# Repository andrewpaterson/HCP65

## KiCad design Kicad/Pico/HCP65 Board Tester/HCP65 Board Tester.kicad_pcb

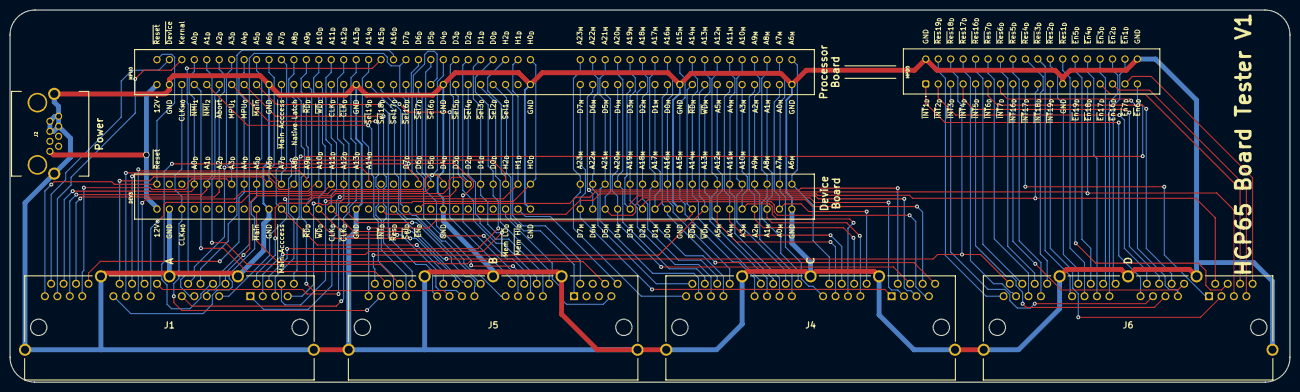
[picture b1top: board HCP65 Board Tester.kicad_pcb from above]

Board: 2 copper layers, 261.1 x 75.9 mm, 8 parts (0 on the bottom side), 127 nets.

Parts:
DEV3: 395-098-520-350; 395098520350
J1, J4, J5, J6: 6339167-2; 63391672
J2: 1-406541-1; 1-406541-1_1
MPD0: 2-5530843-7; 255308437
MPU0: 395-098-520-350; 395098520350

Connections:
/12V: DEV3.B1, J2.1, MPU0.B1
/A0_{D}: DEV3.A4, J1.D4, MPU0.A4
/A0_{M}: DEV3.D17, J4.B8, MPU0.D17
/A1_{D}: DEV3.A5, J1.D5, MPU0.A5
/A1_{M}: DEV3.D16, J4.B7, MPU0.D16
/A2_{D}: DEV3.A6, J1.D6, MPU0.A6
/A2_{M}: DEV3.D15, J4.B6, MPU0.D15
/A3_{D}: DEV3.A7, J1.D7, MPU0.A7
/A3_{M}: DEV3.D14, J4.B5, MPU0.D14
/A4_{D}: DEV3.A8, J1.D8, MPU0.A8
/A4_{M}: DEV3.D13, J4.B4, MPU0.D13
/A5_{D}: DEV3.A9, J1.C1, MPU0.A9
/A5_{M}: DEV3.D12, J4.B3, MPU0.D12
/A6_{D}: DEV3.A10, J1.C2, MPU0.A10
/A6_{M}: DEV3.C18, J4.B2, MPU0.C18
/A7_{D}: DEV3.A11, J1.C3, MPU0.A11
/A7_{M}: DEV3.C17, J4.B1, MPU0.C17
/A8_{D}: DEV3.A12, J1.C4, MPU0.A12
/A8_{M}: DEV3.C16, J4.C8, MPU0.C16
/A9_{D}: DEV3.A13, J1.C5, MPU0.A13
/A9_{M}: DEV3.C15, J4.C7, MPU0.C15
/A10_{D}: DEV3.A14, J1.C6, MPU0.A14
/A10_{M}: DEV3.C14, J4.C6, MPU0.C14
/A11_{D}: DEV3.A15, J1.C7, MPU0.A15
/A11_{M}: DEV3.C13, J4.C5, MPU0.C13
/A12_{D}: DEV3.A16, J1.C8, MPU0.A16
/A12_{M}: DEV3.C12, J4.C4, MPU0.C12
/A13_{D}: DEV3.A17, J1.B1, MPU0.A17
/A13_{M}: DEV3.C11, J4.C3, MPU0.C11
/A14_{D}: DEV3.A18, J1.B2, MPU0.A18
/A14_{M}: DEV3.C10, J4.C2, MPU0.C10
/A15_{D}: J1.B3, MPU0.A19
/A15_{M}: DEV3.C9, J4.C1, MPU0.C9
/A16_{D}: J1.B4, MPU0.A20
/A16_{M}: DEV3.C8, J4.D8, MPU0.C8
/A17_{M}: DEV3.C7, J4.D7, MPU0.C7
/A18_{M}: DEV3.C6, J4.D6, MPU0.C6
/A19_{M}: DEV3.C5, J4.D5, MPU0.C5
/A20_{M}: DEV3.C4, J4.D4, MPU0.C4
/A21_{M}: DEV3.C3, J4.D3, MPU0.C3
/A22_{M}: DEV3.C2, J4.D2, MPU0.C2
/A23_{M}: DEV3.C1, J4.D1, MPU0.C1
/CLK_{D}: DEV3.B15, J5.C6, MPU0.B15
/CLK_{M0}: DEV3.B3, J5.D3, MPU0.B3
/D0_{D}: DEV3.A28, J1.A4, MPU0.A28
/D0_{M}: DEV3.D8, J4.A8, MPU0.D8
/D1_{D}: DEV3.A27, J1.A3, MPU0.A27
/D1_{M}: DEV3.D7, J4.A7, MPU0.D7
/D2_{D}: DEV3.A26, J1.A2, MPU0.A26
/D2_{M}: DEV3.D6, J4.A6, MPU0.D6
/D3_{D}: DEV3.A25, J1.A1, MPU0.A25
/D3_{M}: DEV3.D5, J4.A5, MPU0.D5
/D4_{D}: DEV3.A24, J1.B8, MPU0.A24
/D4_{M}: DEV3.D4, J4.A4, MPU0.D4
/D5_{D}: DEV3.A23, J1.B7, MPU0.A23
/D5_{M}: DEV3.D3, J4.A3, MPU0.D3
/D6_{D}: DEV3.A22, J1.B6, MPU0.A22
/D6_{M}: DEV3.D2, J4.A2, MPU0.D2
/D7_{D}: DEV3.A21, J1.B5, MPU0.A21
/D7_{M}: DEV3.D1, J4.A1, MPU0.D1
/GND: DEV3.B2, DEV3.B10, DEV3.B17, DEV3.B24, DEV3.B31, DEV3.D9, DEV3.D18, J1.MH1, J1.MH2, J1.MH3, J1.MH4, J1.MH5, J2.5, J2.6, J2.7, J2.8, J2.MH1, J2.MH2, J4.MH1, J4.MH2, J4.MH3, J4.MH4, J4.MH5, J5.MH1, J5.MH2, J5.MH3, J5.MH4, J5.MH5, J6.MH1, J6.MH2, J6.MH3, J6.MH4, J6.MH5, MPD0.2, MPD0.23, MPD0.36, MPU0.B2, MPU0.B10, MPU0.B17, MPU0.B24, MPU0.B31, MPU0.D9, MPU0.D18
/H0_{D}: DEV3.A31, J1.A7, MPU0.A31
/H1_{D}: DEV3.A30, J1.A6, MPU0.A30
/H2_{D}: DEV3.A29, J1.A5, MPU0.A29
/Kernal: J1.D3, MPU0.A3
/MPU0_{M}: J5.D8, MPU0.B8
/MPU1_{M}: J5.D7, MPU0.B7
/Native Latch: J5.C3, MPU0.B12
/~ABORT: J5.D6, MPU0.B6
/~CLK_{D}: DEV3.B16, J5.C7, MPU0.B16
/~Device: J1.D2, MPU0.A2
/~Enable_{Device}1: J6.C8, MPD0.34
/~Enable_{Device}2: J6.C7, MPD0.32
/~Enable_{Device}3: J6.C6, MPD0.30
/~Enable_{Device}4: J6.C5, MPD0.28
/~Enable_{Device}5: J6.C4, MPD0.26
/~Enable_{Device}6: J1.A8, MPD0.35
/~Enable_{Device}7: J6.A8, MPD0.33
/~Enable_{Device}16: J6.A7, MPD0.31
/~Enable_{Device}17: J6.A6, MPD0.29
/~Enable_{Device}18: DEV3.B22, J6.A5, MPD0.27
/~Enable_{Device}19: J6.A4, MPD0.25
/~Interrupt_{Device}1: J6.B1, MPD0.1
/~Interrupt_{Device}2: J6.B2, MPD0.3
/~Interrupt_{Device}3: J6.B3, MPD0.5
/~Interrupt_{Device}4: J6.B4, MPD0.7
/~Interrupt_{Device}5: J6.B5, MPD0.9
/~Interrupt_{Device}6: J6.B6, MPD0.11
/~Interrupt_{Device}7: J6.B7, MPD0.13
/~Interrupt_{Device}16: J6.B8, MPD0.15
/~Interrupt_{Device}17: J6.A1, MPD0.17
/~Interrupt_{Device}18: DEV3.B19, J6.A2, MPD0.19
/~Interrupt_{Device}19: J6.A3, MPD0.21
/~Main Access_{M0}: DEV3.B11, J5.C2, MPU0.B11
/~Main3: DEV3.B9, J5.A6
/~Main MPU: J5.C1, MPU0.B9
/~Memory Hi_{ Device}: DEV3.B30, J5.A8
/~Memory Lo_{ Device}: DEV3.B29, J5.A7
/~NMI_{1}: J5.D4, MPU0.B4
/~NMI_{2}: J5.D5, MPU0.B5
/~RD_{D}: DEV3.B13, J5.C4, MPU0.B13
/~RD_{M}: DEV3.D10, J5.D1, MPU0.D10
/~Reset: DEV3.A1, J1.D1, MPU0.A1
/~Reset_{Device}1: J6.C3, MPD0.24
/~Reset_{Device}2: J6.C2, MPD0.22
/~Reset_{Device}3: J6.C1, MPD0.20
/~Reset_{Device}4: J6.D8, MPD0.18
/~Reset_{Device}5: J6.D7, MPD0.16
/~Reset_{Device}6: J6.D6, MPD0.14
/~Reset_{Device}7: J6.D5, MPD0.12
/~Reset_{Device}16: J6.D4, MPD0.10
/~Reset_{Device}17: J6.D3, MPD0.8
/~Reset_{Device}18: DEV3.B20, J6.D2, MPD0.6
/~Reset_{Device}19: J6.D1, MPD0.4
/~Select_{Device}1: J5.A2, MPU0.B29
/~Select_{Device}2: J5.A1, MPU0.B28
/~Select_{Device}3: J5.B8, MPU0.B27
/~Select_{Device}4: J5.B7, MPU0.B26
/~Select_{Device}5: J5.B6, MPU0.B25
/~Select_{Device}6: J5.B5, MPU0.B23
/~Select_{Device}7: J5.B4, MPU0.B22
/~Select_{Device}16: J5.B3, MPU0.B21
/~Select_{Device}17: J5.B2, MPU0.B20
/~Select_{Device}18: DEV3.B21, J5.B1, MPU0.B19
/~Select_{Device}19: J5.C8, MPU0.B18
/~WD_{D}: DEV3.B14, J5.C5, MPU0.B14
/~WD_{M}: DEV3.D11, J5.D2, MPU0.D11

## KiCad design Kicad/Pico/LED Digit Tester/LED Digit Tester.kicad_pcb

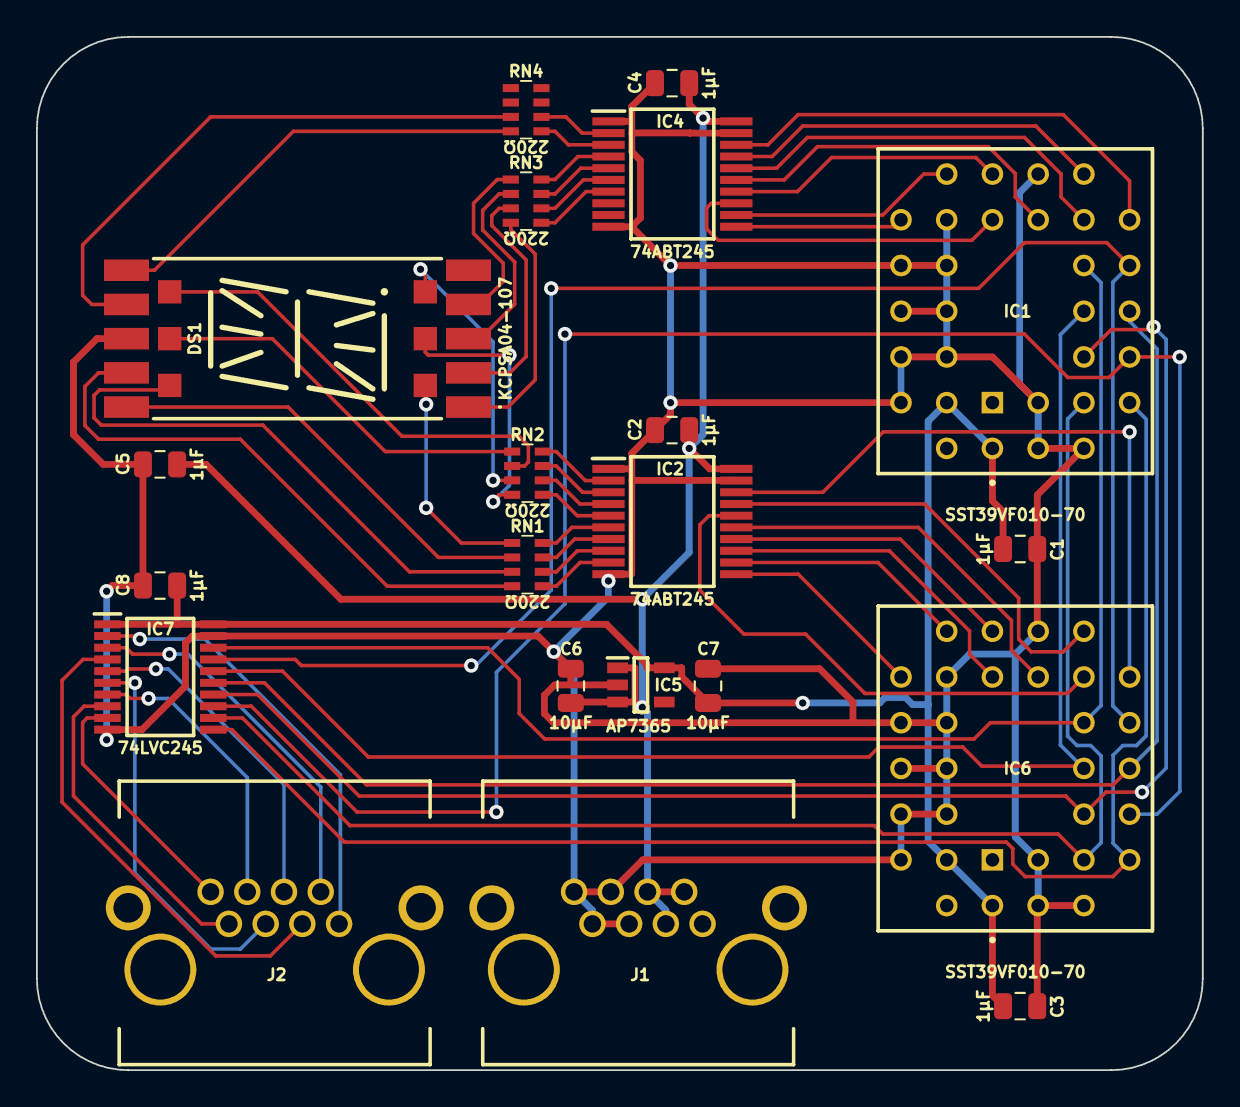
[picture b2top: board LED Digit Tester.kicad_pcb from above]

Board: 2 copper layers, 64.8 x 57.4 mm, 21 parts (0 on the bottom side), 63 nets.

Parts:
C1, C2, C3, C4, C5, C8: 1μF; C_0805
C6, C7: 10µF; C_0805
DS1: KCPSA04-107; KCPSA04107
IC1, IC6: SST39VF010-70-4I-NHE; 5408803224008
IC2, IC4: SN74ABT245BDBR; SOP65P780X200-20N
IC5: AP7365-33WG-7; SOT95P285X130-5N
IC7: 74LVC245AT20; SOP65P640X120-20N
J1, J2: 1-406541-1; 1-406541-1_1
RN1, RN2, RN3, RN4: CAY16-221J4LF; CAY16-F4

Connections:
/3.3V: C1.1, C3.1, C7.1, C8.1, IC1.31 (~WE), IC1.32 (3V), IC5.5 (3.3VOut), IC6.31 (~WE), IC6.32 (3V), IC7.1 (DIR), IC7.20 (3V)
/5V: C2.1, C4.1, C5.1, C6.1, IC2.20 (5V), IC4.20 (5V), IC5.1 (6VIn), IC5.3 (EN), J1.2, J1.3, J1.4
/A0: IC1.12 (A0), IC6.12 (A0), IC7.18 (B0)
/A1: IC1.11 (A1), IC6.11 (A1), IC7.17 (B1)
/A2: IC1.10 (A2), IC6.10 (A2), IC7.16 (B2)
/A3: IC1.9 (A3), IC6.9 (A3), IC7.15 (B3)
/A4: IC1.8 (A4), IC6.8 (A4), IC7.14 (B4)
/A5: IC1.7 (A5), IC6.7 (A5), IC7.13 (B5)
/A6: IC1.6 (A6), IC6.6 (A6), IC7.12 (B6)
/A7: IC1.5 (A7), IC6.5 (A7), IC7.11 (B7)
/GND: C1.2, C2.2, C3.2, C4.2, C5.2, C6.2, C7.2, C8.2, DS1.14 (Cathode), IC1.2 (A16), IC1.3 (A15), IC1.4 (A12), IC1.16 (GND), IC1.22 (~CE), IC1.23 (A10), IC1.24 (~OE), IC1.25 (A11), IC1.26 (A9), IC1.27 (A8), IC1.28 (A13), IC1.29 (A14), IC2.1 (DIR), IC2.10 (GND), IC2.19 (~OE), IC4.1 (DIR), IC4.10 (GND), IC4.19 (~OE), IC5.2 (GND), IC6.2 (A16), IC6.3 (A15), IC6.4 (A12), IC6.16 (GND), IC6.22 (~CE), IC6.23 (A10), IC6.24 (~OE), IC6.25 (A11), IC6.26 (A9), IC6.27 (A8), IC6.28 (A13), IC6.29 (A14), IC7.10 (GND), IC7.19 (~OE), J1.5, J1.6, J1.7, J1.8
/LED A-Seg: IC2.2 (A0), RN2.8 (R1)
/LED B-Seg: IC2.3 (A1), RN2.7 (R2)
/LED C-Seg: IC2.4 (A2), RN2.6 (R3)
/LED D-Seg: IC2.5 (A3), RN2.5 (R4)
/LED E-Seg: IC2.6 (A4), RN1.8 (R1)
/LED F-Seg: IC2.7 (A5), RN1.7 (R2)
/LED G-Seg: IC2.8 (A6), RN1.6 (R3)
/LED H-Seg: IC2.9 (A7), RN1.5 (R4)
/LED J-Seg: IC4.2 (A0), RN4.6 (R3)
/LED K-Seg: IC4.3 (A1), RN4.5 (R4)
/LED L-Seg: IC4.4 (A2), RN3.8 (R1)
/LED M-Seg: IC4.5 (A3), RN3.7 (R2)
/LED N-Seg: IC4.6 (A4), RN3.6 (R3)
/LED P-Seg: IC4.7 (A5), RN3.5 (R4)
/LED Ω A-Seg: DS1.10 (A-Seg), RN2.1 (R1)
/LED Ω B-Seg: DS1.11 (B-Seg), RN2.2 (R2)
/LED Ω C-Seg: DS1.6 (C-Seg), RN2.3 (R3)
/LED Ω D-Seg: DS1.7 (D-Seg), RN2.4 (R4)
/LED Ω E-Seg: DS1.8 (E-Seg), RN1.1 (R1)
/LED Ω F-Seg: DS1.16 (F-Seg), RN1.2 (R2)
/LED Ω G-Seg: DS1.9 (G-Seg), RN1.3 (R3)
/LED Ω H-Seg: DS1.15 (H-Seg), RN1.4 (R4)
/LED Ω J-Seg: DS1.13 (J-Seg), RN4.3 (R3)
/LED Ω K-Seg: DS1.12 (K-Seg), RN4.4 (R4)
/LED Ω L-Seg: DS1.4 (L-Seg), RN3.1 (R1)
/LED Ω M-Seg: DS1.3 (M-Seg), RN3.2 (R2)
/LED Ω N-Seg: DS1.2 (N-Seg), RN3.3 (R3)
/LED Ω P-Seg: DS1.1 (P-Seg), RN3.4 (R4)
/OP0: IC7.2 (A0), J2.1
/OP1: IC7.3 (A1), J2.2
/OP2: IC7.4 (A2), J2.3
/OP3: IC7.5 (A3), J2.4
/OP4: IC7.6 (A4), J2.5
/OP5: IC7.7 (A5), J2.6
/OP6: IC7.8 (A6), J2.7
/OP7: IC7.9 (A7), J2.8
unnamed: IC1.13 (DQ0), IC4.18 (B0)
unnamed: IC1.14 (DQ1), IC4.17 (B1)
unnamed: IC1.15 (DQ2), IC4.16 (B2)
unnamed: IC1.17 (DQ3), IC4.15 (B3)
unnamed: IC1.18 (DQ4), IC4.14 (B4)
unnamed: IC1.19 (DQ5), IC4.13 (B5)
unnamed: IC1.20 (DQ6), IC4.12 (B6)
unnamed: IC1.21 (DQ7), IC4.11 (B7)
unnamed: IC2.18 (B0), IC6.13 (DQ0)
unnamed: IC2.17 (B1), IC6.14 (DQ1)
unnamed: IC2.16 (B2), IC6.15 (DQ2)
unnamed: IC2.15 (B3), IC6.17 (DQ3)
unnamed: IC2.14 (B4), IC6.18 (DQ4)
unnamed: IC2.13 (B5), IC6.19 (DQ5)
unnamed: IC2.12 (B6), IC6.20 (DQ6)
unnamed: IC2.11 (B7), IC6.21 (DQ7)

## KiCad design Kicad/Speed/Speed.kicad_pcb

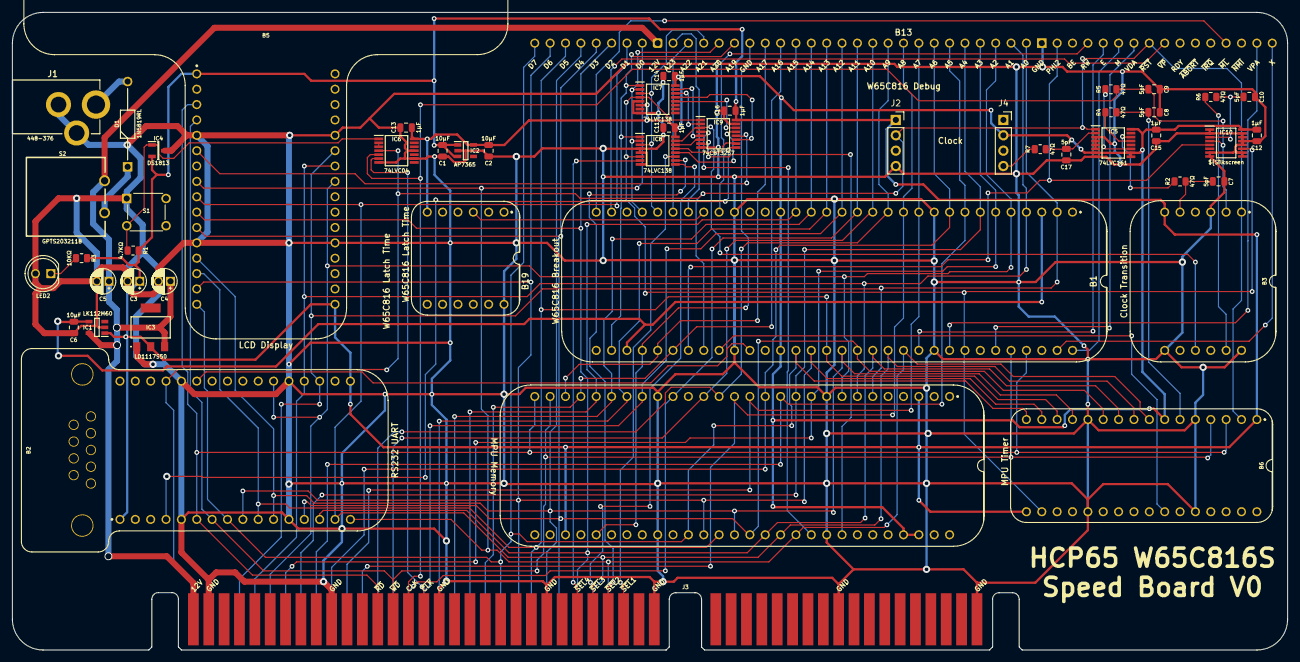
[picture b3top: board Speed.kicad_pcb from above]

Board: 2 copper layers, 210.8 x 105.4 mm, 50 parts (0 on the bottom side), 89 nets.

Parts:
B1: W65C816 Breakout; HCP65_W65C816_Breakout
B2: UART RS232; HCP65_RS232_UART
B3: Clock Transition; HCP65_Clock_Transition
B4: MPU Memory; HCP65_MPU_Memory
B5: LCD Display; HCP65_LCD_Display
B6: MPU Timer; HCP65_MPU_Timer
B13: W65C816 Debug; HCP65_W65C816_Debug_Display
B19: W65C816_Latch_Time; HCP65_W65C816_Latch_Time
C1, C2, C6: 10µF; C_0805
C3: 100μF; CP_Radial_D4.0mm_P2.00mm
C4, C5: 10μF; CP_Radial_D4.0mm_P2.00mm
C7, C8, C9, C10, C17: 5pF; C_0805
C11, C12, C13, C14, C15, C16: 1µF; C_0805
D1: 1N5819RL; DIOAD1414W86L464D238
IC1: LK112M60TR; SOT95P285X130-5N
IC2: AP7365-33WG-7; SOT95P285X130-5N
IC3: LD1117S50C; LD1117S33C
IC4: DS1813R-10+T&R; SOT95P237X112-3N
IC5: 74LVC161PW,112; SOP65P640X110-16N
IC6: 74LVC04APW,118; SOP65P640X110-14N
IC7, IC8: 74LVC138APW-Q100J; SOP65P640X110-16N
IC9: SN74CBT3257CPWR; SOP65P640X120-16N
IC10: PI3B3251QE; SOP64P599X175-16N
J1: 448-376; 448376
J2, J4: Conn_01x04_Socket; PinSocket_1x04_P2.54mm_Vertical
J3: 395-098-520-350; 98pin Edge Connector
LED2: Red; LED_D5.0mm
R1: 4.7KΩ; R_0805
R2, R4, R5, R6, R7: 47Ω; R_0805
R3: 10KΩ; R_0805
S1: DTS-62N-V; DTS62NV
S2: GPTS203211B

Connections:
6.25MHZ: B3.2 (Slow_Clock), C9.1, IC6.5 (3A), IC10.4 (I0), J3.B15, R5.1
12V: B13.9 (12V), C4.1, C5.1, IC1.5 (14VIn), IC3.3 (15VIn), J3.B1, S2.2
/3.3V: B1.20 (BE), B1.45 (DE), B4.53 (~Special), B4.54 (~Main), B6.7 (~NMI_Rate_Select), B19.6 (3.3V), C2.1, C11.1, C12.1, C13.1, C14.1, C15.1, IC2.5 (3.3VOut), IC5.7 (CEP), IC5.9 (~PE), IC5.10 (CET), IC5.16 (3V), IC6.14 (3V), IC7.6 (E3), IC7.16 (3V), IC8.16 (3V), IC10.16 (3V), J4.2
/5V: B2.1 (5V), B2.17 (5V), B3.6 (5V), B4.3 (5V), B4.31 (5V), B5.1 (5V), B5.17 (5V), B6.1 (5V), B6.17 (5V), C1.1, C3.1, C16.1, IC1.1 (~SHDN), IC2.1 (6VIn), IC2.3 (EN), IC3.2 (5.0VOut), IC3.4 (5.0VOut), IC4.2 (5V), IC9.16 (5V), J2.1, R1.2, R3.2
/12V Forward: D1.1, S2.1
/12V Socket: D1.2, J1.INNER (VCC)
/25MHZ: B6.6 (CLK), C8.1, R4.1
/50MHZ: B3.5 (Fast_Clock), C7.1, R2.1
/A17: B1.37 (BA1), B4.26 (A17), B13.16 (A17)
/A18: B1.36 (BA2), B4.33 (A18), B13.15 (A18)
/A19: B1.34 (BA3), B13.14 (A19), IC7.1 (A0), IC8.1 (A0)
/A20: B1.29 (BA4), B13.13 (A20), IC7.2 (A1), IC8.2 (A1)
/A21: B1.28 (BA5), B13.12 (A21), IC7.3 (A2), IC8.3 (A2)
/A22: B1.27 (BA6), B13.11 (A22)
/A23: B1.26 (BA7), B13.10 (A23)
/Address Valid: B1.22 (Address_Valid), IC6.13 (6A)
/Bank Latch: B1.30 (Bank_Latch), B19.9 (~Data_Output)
/CLK: J4.4, R7.2
/Clock: C10.1, IC10.3 (I1), R6.1
/E: B1.54 (E), B13.38 (E)
/M: B1.64 (M), B13.39 (M)
/Native Latch: B1.57 (Native_Latch), B6.18 (~Hold), IC7.4 (~E1), IC8.6 (E3), IC9.1 (S), IC10.11 (S0)
/PHI2: B1.39 (PHI2), B13.35 (PHI2), IC10.5 (Y)
/Reset: IC6.2 (1Y), IC6.3 (2A)
/R~W: B1.24 (R~W), B13.37 (R~W)
/VDA: B1.59 (VDA), B13.40 (VDA)
/VPA: B1.56 (VPA), B13.48 (VPA)
/W65C816V: B1.3 (5V), B1.35 (5V), C6.1, IC1.4 (5.0VOut)
/X: B1.63 (X), B13.49 (X)
/~Address Valid: B4.1 (~Address_Valid), IC6.12 (6Y)
/~INT: B1.43 (~IRQ), B2.27 (~INT)
/~LCD: B5.6 (~CS), IC9.12 (4A)
/~LCD_{E}: IC7.12 (~Y3), IC9.14 (4B1)
/~LCD_{N}: IC8.12 (~Y3), IC9.13 (4B2)
/~ML: B1.32 (~ML), B13.46 (~ML)
/~NMI: B1.41 (~NMI), B6.26 (~Set_Timer)
/~PHI2: B1.25 (~PHI2_{OUT}), B19.3 (~PHI2)
/~RAM: B4.47 (~RAM), IC9.4 (1A)
/~RAM_{E}: IC7.14 (~Y1), IC9.2 (1B1)
/~RAM_{N}: B3.9 (~Select_Fast), IC8.15 (~Y0), IC9.3 (1B2)
/~ROM: B4.49 (~ROM), IC9.7 (2A)
/~ROM_{E}: IC7.15 (~Y0), IC9.5 (2B1)
/~ROM_{N}: IC8.14 (~Y1), IC9.6 (2B2)
/~Reset Switch: IC4.1 (~RST), IC6.1 (1A), R1.1, S1.3 (N1)
/~Trans Out: B1.58 (~Data_Output), B19.10 (Bank_Latch)
/~UART: B2.4 (~CS), IC9.9 (3A)
/~UART_{E}: IC7.13 (~Y2), IC9.11 (3B1)
/~UART_{N}: IC8.13 (~Y2), IC9.10 (3B2)
/~VP: B1.31 (~VP), B13.42 (~VP)
A0: B1.2 (A0), B2.19 (A0), B4.6 (A0), B5.27 (A0), B13.33 (A0), J3.A4
A1: B1.4 (A1), B2.20 (A1), B4.7 (A1), B5.26 (A1), B13.32 (A1), J3.A5
A2: B1.5 (A2), B2.22 (A2), B4.8 (A2), B5.25 (A2), B13.31 (A2), J3.A6
A3: B1.6 (A3), B4.10 (A3), B13.30 (A3), J3.A7
A4: B1.7 (A4), B4.11 (A4), B13.29 (A4), J3.A8
A5: B1.8 (A5), B4.12 (A5), B13.28 (A5), J3.A9
A6: B1.9 (A6), B4.13 (A6), B13.27 (A6), J3.A10
A7: B1.11 (A7), B4.14 (A7), B13.26 (A7), J3.A11
A8: B1.12 (A8), B4.15 (A8), B13.25 (A8), J3.A12
A9: B1.13 (A9), B4.16 (A9), B13.24 (A9), J3.A13
A10: B1.14 (A10), B4.17 (A10), B13.23 (A10), J3.A14
A11: B1.15 (A11), B4.19 (A11), B13.22 (A11), J3.A15
A12: B1.16 (A12), B4.21 (A12), B13.21 (A12), J3.A16
A13: B1.17 (A13), B4.22 (A13), B13.20 (A13), J3.A17
A14: B1.18 (A14), B4.23 (A14), B13.19 (A14), J3.A18
A15: B1.19 (A15), B4.24 (A15), B13.18 (A15), J3.A19
A16: B1.38 (BA0), B4.25 (A16), B13.17 (A16), J3.A20
D0: B1.53 (D0), B2.16 (D0), B4.46 (D0), B5.8 (D0), B6.8 (D0), B13.8 (D0), J3.A28
D1: B1.52 (D1), B2.15 (D1), B4.45 (D1), B5.9 (D1), B6.9 (D1), B13.7 (D1), J3.A27
D2: B1.51 (D2), B2.14 (D2), B4.44 (D2), B5.10 (D2), B6.10 (D2), B13.6 (D2), J3.A26
D3: B1.50 (D3), B2.13 (D3), B4.43 (D3), B5.11 (D3), B6.11 (D3), B13.5 (D3), J3.A25
D4: B1.49 (D4), B2.11 (D4), B4.42 (D4), B5.13 (D4), B6.13 (D4), B13.4 (D4), J3.A24
D5: B1.48 (D5), B2.10 (D5), B4.41 (D5), B5.14 (D5), B6.14 (D5), B13.3 (D5), J3.A23
D6: B1.47 (D6), B2.9 (D6), B4.40 (D6), B5.15 (D6), B6.15 (D6), B13.2 (D6), J3.A22
D7: B1.46 (D7), B2.8 (D7), B4.39 (D7), B5.16 (D7), B6.16 (D7), B13.1 (D7), J3.A21
GND: B1.10 (GND), B1.23 (GND), B1.42 (GND), B1.55 (GND), B2.5 (GND), B2.12 (GND), B2.21 (GND), B2.28 (GND), B3.3 (GND), B3.7 (GND), B3.12 (GND), B4.9 (GND), B4.20 (GND), B4.37 (GND), B4.48 (GND), B5.5 (GND), B5.12 (GND), B5.21 (GND), B5.28 (GND), B6.5 (GND), B6.12 (GND), B6.21 (GND), B6.28 (GND), B13.34 (GND), B19.12 (GND), C1.2, C2.2, C3.2, C4.2, C5.2, C6.2, C7.2, C8.2, C9.2, C10.2, C11.2, C12.2, C13.2, C14.2, C15.2, C16.2, C17.2, IC1.2 (GND), IC2.2 (GND), IC3.1 (GND), IC4.3 (GND), IC5.3 (D0), IC5.4 (D1), IC5.5 (D2), IC5.6 (D3), IC5.8 (GND), IC6.7 (GND), IC6.9 (4A), IC6.11 (5A), IC7.5 (~E2), IC7.8 (GND), IC8.4 (~E1), IC8.5 (~E2), IC8.8 (GND), IC9.8 (GND), IC9.15 (~OE), IC10.1 (I3), IC10.2 (I2), IC10.7 (~OE), IC10.8 (GND), IC10.9 (S2), IC10.10 (S1), IC10.12 (I7), IC10.13 (I6), IC10.14 (I5), IC10.15 (I4), J1.SHL1 (GND), J1.SHL2 (GND), J2.4, J3.B2, J3.B10, J3.B17, J3.B24, J3.B31, J3.D9, J3.D18, LED2.2 (A), S1.1 (C1)
unnamed: B3.11 (Clock), R6.2
unnamed: C17.1, IC5.2 (CP), R7.1
unnamed: IC5.14 (Q0), R2.2
unnamed: IC5.13 (Q1), R4.2
unnamed: IC5.11 (Q3), R5.2
unnamed: LED2.1 (K), R3.1
~6.25MHZ: IC6.6 (3Y), J3.B16
~RD: B1.61 (~RD), B2.6 (~RD), B4.28 (~RD), B5.3 (~RD), B6.3 (~RD), J3.B13
~Reset: B1.40 (~Reset), B2.29 (~Reset), B3.1 (~Reset), B6.2 (~Reset), B13.41 (~RES), IC5.1 (~MR), IC6.4 (2Y), J2.2, J3.A1
~Select_{Device}1: IC8.11 (~Y4), J3.B29
~Select_{Device}2: IC8.10 (~Y5), J3.B28
~Select_{Device}3: IC8.9 (~Y6), J3.B27
~Select_{Device}4: IC8.7 (~Y7), J3.B26
~WD: B1.60 (~WD), B2.7 (~WD), B4.27 (~WD), B5.4 (~WD), B6.4 (~WD), J3.B14

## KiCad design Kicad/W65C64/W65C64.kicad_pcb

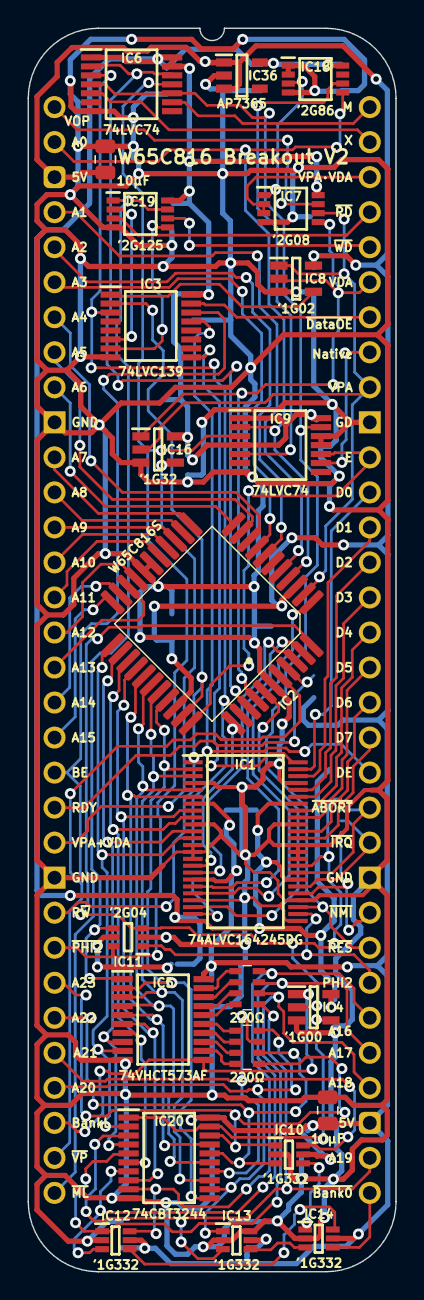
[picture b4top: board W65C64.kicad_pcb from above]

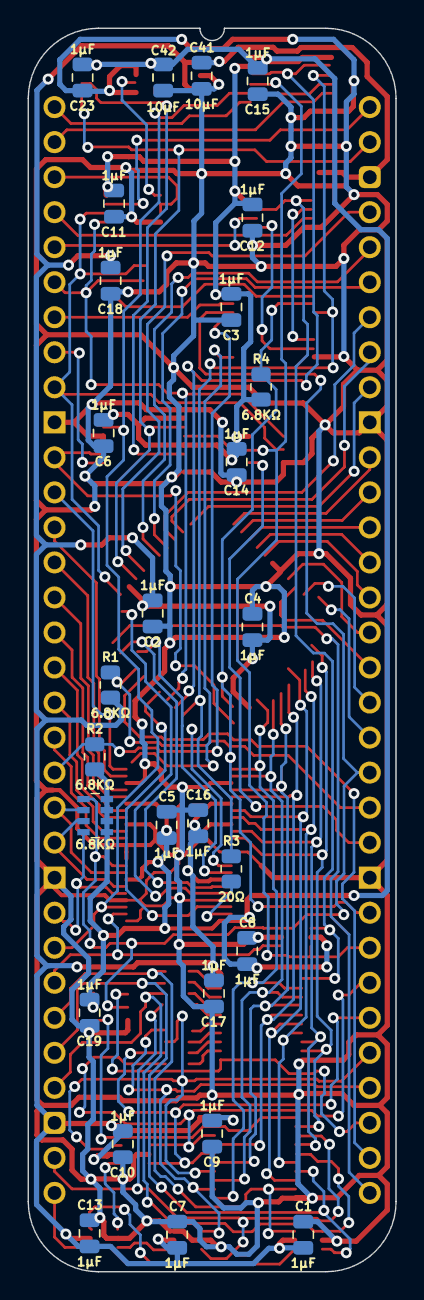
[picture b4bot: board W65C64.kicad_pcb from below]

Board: 2 copper layers, 26.7 x 90.2 mm, 51 parts (27 on the bottom side), 96 nets.

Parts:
C1, C2, C3, C4, C5, C6, C7, C8, C9, C10, C11, C12, C13, C14, C15, C16, C17, C18, C19, C23: 1μF; C_0805
C20, C21, C41, C42: 10μF; C_0805
IC1: 74ALVC164245DGG,11; SOP50P810X120-48N
IC2: W65C816S6TQG-14; W65C816 PLCC 0.8mm 44 Pin
IC3: 74LVC139PW,118; SOP65P640X110-16N
IC4: 74LVC1G00GV,125; SOT95P275X110-5N
IC5: 74VHCT573AFT; SOP65P640X120-20N
IC6, IC9: 74LVC74APW,118; SOP65P640X110-14N
IC7: 74LVC2G08DP-Q100H; SOP65P400X110-8N
IC8: 74LVC1G02GV,125; SOT95P275X110-5N
IC10, IC12, IC13, IC14: SN74LVC1G332DCKRG4; SOT65P210X110-6N
IC11: 74LVC2G04GW-Q100H; SOP65P210X110-6N
IC16: 74LVC1G32GV,125; SOT95P275X110-5N
IC18: 74LVC2G86DP,125; SOP65P400X110-8N
IC19: 74LVC2G125DP,125; SOP65P400X110-8N
IC20: SN74CBT3244CPWR; SOP65P640X120-20N
IC36: AP7365-33WG-7; SOT95P285X130-5N
J7: Board 2x32 W22.86mm; DIP-64_Board_W22.86mm
R1, R2, R4: 6.8KΩ; R_0805
R3: 20Ω; R_0805
RN1, RN2: CAY16-221J4LF; CAY16-F4
RN4: CAY16-472J4LF; CAY16-F4

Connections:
5V: C1.1, C2.1, C4.1, C7.1, C9.1, C10.1, C13.1, C16.1, C17.1, C18.1, C20.1, C21.1, C41.1, IC1.7 (5V), IC1.18 (5V), IC2.9 (VCC), IC2.37 (VCC), IC5.20 (5V), IC8.5 (3V), IC10.5 (3V), IC12.5 (3V), IC13.5 (3V), IC14.5 (3V), IC20.20 (5V), IC36.1 (6VIn), IC36.3 (EN), J7.3, J7.35, R1.1
/3.3V: C3.1, C5.1, C6.1, C8.1, C11.1, C12.1, C14.1, C15.1, C19.1, C23.1, C42.1, IC1.24 (2DIR), IC1.31 (3V), IC1.42 (3V), IC3.16 (3V), IC4.5 (3V), IC6.1 (~1RD), IC6.13 (~2RD), IC6.14 (3V), IC7.8 (3V), IC9.1 (~1RD), IC9.4 (~1SD), IC9.14 (3V), IC11.5 (3V), IC16.5 (3V), IC18.8 (VCC), IC19.8 (VCC), IC36.5 (3.3VOut), R2.1, R4.1, RN4.1 (R1), RN4.2 (R2), RN4.3 (R3), RN4.4 (R4)
/A0_{CHANGE}: IC7.1 (1A), IC18.3 (2Y)
/A0_{PREV}: IC9.5 (1Q), IC18.6 (2B)
/BA0+BA1+BA2: IC12.4 (Y), IC14.6 (C)
/BA3+BA4: IC13.4 (Y), IC14.3 (B)
/BA5+BA6+BA7: IC10.4 (Y), IC14.1 (A)
/BE_{5V}: IC1.16 (2B2), IC2.40 (BE)
/D0_{65}: IC1.2 (1B0), IC2.36 (D0), IC5.2 (D0), IC20.11 (2A1)
/D0_{VHC}: IC5.19 (Q0), RN2.1 (R1)
/D1_{65}: IC1.3 (1B1), IC2.35 (D1), IC5.3 (D1), IC20.13 (2A2)
/D1_{VHC}: IC5.18 (Q1), RN2.2 (R2)
/D2_{65}: IC1.5 (1B2), IC2.34 (D2), IC5.4 (D2), IC20.15 (2A3)
/D2_{VHC}: IC5.17 (Q2), RN2.3 (R3)
/D3_{65}: IC1.6 (1B3), IC2.33 (D3), IC5.5 (D3), IC20.17 (2A4)
/D3_{VHC}: IC5.16 (Q3), RN2.4 (R4)
/D4_{65}: IC1.8 (1B4), IC2.32 (D4), IC5.6 (D4), IC20.8 (1A4)
/D4_{VHC}: IC5.15 (Q4), RN1.1 (R1)
/D5_{65}: IC1.9 (1B5), IC2.31 (D5), IC5.7 (D5), IC20.6 (1A3)
/D5_{VHC}: IC5.14 (Q5), RN1.2 (R2)
/D6_{65}: IC1.11 (1B6), IC2.30 (D6), IC5.8 (D6), IC20.4 (1A2)
/D6_{VHC}: IC5.13 (Q6), RN1.3 (R3)
/D7_{65}: IC1.12 (1B7), IC2.29 (D7), IC5.9 (D7), IC20.2 (1A1)
/D7_{VHC}: IC5.12 (Q7), RN1.4 (R4)
/FET ~OE: IC4.4 (Y), IC20.1 (1~OE), IC20.19 (2~OE)
/MX: IC2.42 (MX), IC6.2 (1D), IC6.12 (2D)
/PHI2_{5V}: IC2.41 (PHI2), IC3.3 (1A1), IC6.3 (1CP), R3.2
/~ABORT_{5V}: IC1.17 (2B3), IC2.4 (~ABORT)
/~BE: IC5.1 (~OE), IC11.4 (2Y), IC19.1 (1~OE), IC19.7 (2~OE)
/~DE: IC1.48 (1~OE), IC3.9 (~2Y3)
/~IRQ_{5V}: IC1.19 (2B4), IC2.5 (~IRQ)
/~NMI_{5V}: IC1.20 (2B5), IC2.7 (~NMI)
/~RD_{PART}: IC3.7 (~1Y3), IC19.5 (2A)
/~RES_{5V}: IC1.22 (2B6), IC2.44 (~RES)
/~VPA+VDA: IC3.1 (~1E), IC8.4 (Y)
/~WD_{PART}: IC3.6 (~1Y2), IC19.2 (1A)
A0: IC2.10 (A0), IC9.2 (1D), IC18.5 (2A), J7.2
A1: IC2.11 (A1), J7.4
A2: IC2.13 (A2), J7.5
A3: IC2.14 (A3), J7.6
A4: IC2.15 (A4), J7.7
A5: IC2.16 (A5), J7.8
A6: IC2.17 (A6), J7.9
A7: IC2.18 (A7), J7.11
A8: IC2.19 (A8), J7.12
A9: IC2.20 (A9), J7.13
A10: IC2.21 (A10), J7.14
A11: IC2.22 (A11), J7.15
A12: IC2.25 (A12), J7.16
A13: IC2.26 (A13), J7.17
A14: IC2.27 (A14), J7.18
A15: IC2.28 (A15), J7.19
Address Valid: IC16.4 (Y), J7.22
BA0: IC12.6 (C), IC20.9 (2B1), J7.38, RN2.8 (R1)
BA1: IC12.3 (B), IC20.7 (2B2), J7.37, RN2.7 (R2)
BA2: IC12.1 (A), IC20.5 (2B3), J7.36, RN2.6 (R3)
BA3: IC13.3 (B), IC20.3 (2B4), J7.34, RN2.5 (R4)
BA4: IC13.1 (A), IC20.12 (1B4), J7.29, RN1.8 (R1)
BA5: IC10.6 (C), IC20.14 (1B3), J7.28, RN1.7 (R2)
BA6: IC10.3 (B), IC20.16 (1B2), J7.27, RN1.6 (R3)
BA7: IC10.1 (A), IC20.18 (1B1), J7.26, RN1.5 (R4)
BE: IC1.33 (2A2), IC3.14 (2A0), IC4.2 (A), IC11.3 (2A), J7.20, RN4.5 (R4)
Bank Latch: IC4.1 (B), IC5.11 (LE), J7.30
D0: IC1.47 (1A0), J7.53
D1: IC1.46 (1A1), J7.52
D2: IC1.44 (1A2), J7.51
D3: IC1.43 (1A3), J7.50
D4: IC1.41 (1A4), J7.49
D5: IC1.40 (1A5), J7.48
D6: IC1.38 (1A6), J7.47
D7: IC1.37 (1A7), J7.46
DE: IC3.13 (2A1), J7.45, R2.2
E: IC2.39 (E), IC9.10 (~2SD), J7.54
GND: C1.2, C2.2, C3.2, C4.2, C5.2, C6.2, C7.2, C8.2, C9.2, C10.2, C11.2, C12.2, C13.2, C14.2, C15.2, C16.2, C17.2, C18.2, C19.2, C20.2, C21.2, C23.2, C41.2, C42.2, IC1.4 (GND), IC1.10 (GND), IC1.13 (2B0), IC1.14 (2B1), IC1.15 (GND), IC1.21 (GND), IC1.25 (2~OE), IC1.28 (GND), IC1.34 (GND), IC1.35 (2A1), IC1.36 (2A0), IC1.39 (GND), IC1.45 (GND), IC2.1 (GND), IC2.23 (GND), IC2.24 (GND), IC3.8 (GND), IC4.3 (GND), IC5.10 (GND), IC6.7 (GND), IC7.4 (GND), IC8.3 (GND), IC9.7 (GND), IC9.11 (2CP), IC9.12 (2D), IC10.2 (GND), IC11.2 (GND), IC12.2 (GND), IC13.2 (GND), IC13.6 (C), IC14.2 (GND), IC16.3 (GND), IC18.1 (1A), IC18.2 (1B), IC18.4 (GND), IC19.4 (GND), IC20.10 (GND), IC36.2 (GND), J7.10, J7.23, J7.42, J7.55
M: IC6.9 (2Q), J7.64
Native Latch: IC9.9 (2Q), J7.57
unnamed: IC1.23 (2B7), R3.1
Opcode Valid: IC7.7 (1Y), J7.1
PHI2: IC1.26 (2A7), IC11.1 (1A), J7.39
RDY: IC2.3 (RDY), J7.21, R1.2
R~W: IC1.1 (1DIR), IC2.38 (R~W), IC3.2 (1A0), J7.24, R4.2
VDA: IC2.43 (VDA), IC7.5 (2A), IC8.2 (A), IC16.1 (B), J7.59
VPA: IC2.8 (VPA), IC7.6 (2B), IC8.1 (B), IC16.2 (A), J7.56
VPA·VDA: IC7.2 (1B), IC7.3 (2Y), J7.62
X: IC6.5 (1Q), J7.63
~ABORT: IC1.32 (2A3), J7.44, RN4.6 (R3)
~BANK 0: IC14.4 (Y), J7.33
~Data Output: IC3.15 (~2E), J7.58
~IRQ: IC1.30 (2A4), J7.43, RN4.7 (R2)
~ML: IC2.6 (~ML), J7.32
~NMI: IC1.29 (2A5), J7.41, RN4.8 (R1)
~PHI2: IC6.11 (2CP), IC9.3 (1CP), IC11.6 (1Y), J7.25
~RD: IC19.3 (2Y), J7.61
~Reset: IC1.27 (2A6), IC6.4 (~1SD), IC6.10 (~2SD), IC9.13 (~2RD), J7.40
~VP: IC2.2 (~VP), J7.31
~WD: IC19.6 (1Y), J7.60
